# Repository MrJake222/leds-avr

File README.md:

# AVR part of the LEDs project

This is the main project repo. Subfolders contain diffrent parts(LED-RGB, stove, etc.) and (to-be-refactored) common **MODBUS** code in *libs* folder.
**Eagle** folder contains schematics and boards made with *Eagle*

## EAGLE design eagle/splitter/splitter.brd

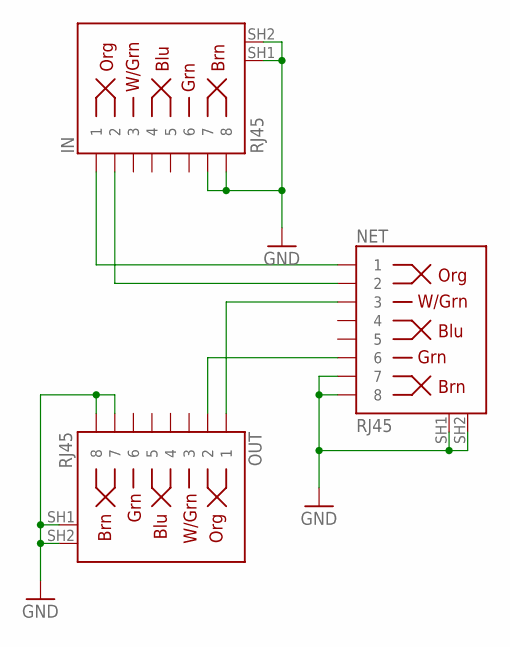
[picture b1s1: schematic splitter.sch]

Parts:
IN: RJ45; RJ45-8
NET: RJ45; RJ45-8
OUT: RJ45; RJ45-8

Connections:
GND: IN.7, IN.8, IN.SH1, IN.SH2, NET.7, NET.8, NET.SH1, NET.SH2, OUT.7, OUT.8, OUT.SH1, OUT.SH2
IN_A: IN.1, NET.1
IN_B: IN.2, NET.2
OUT_A: NET.3, OUT.1
OUT_B: NET.6, OUT.2

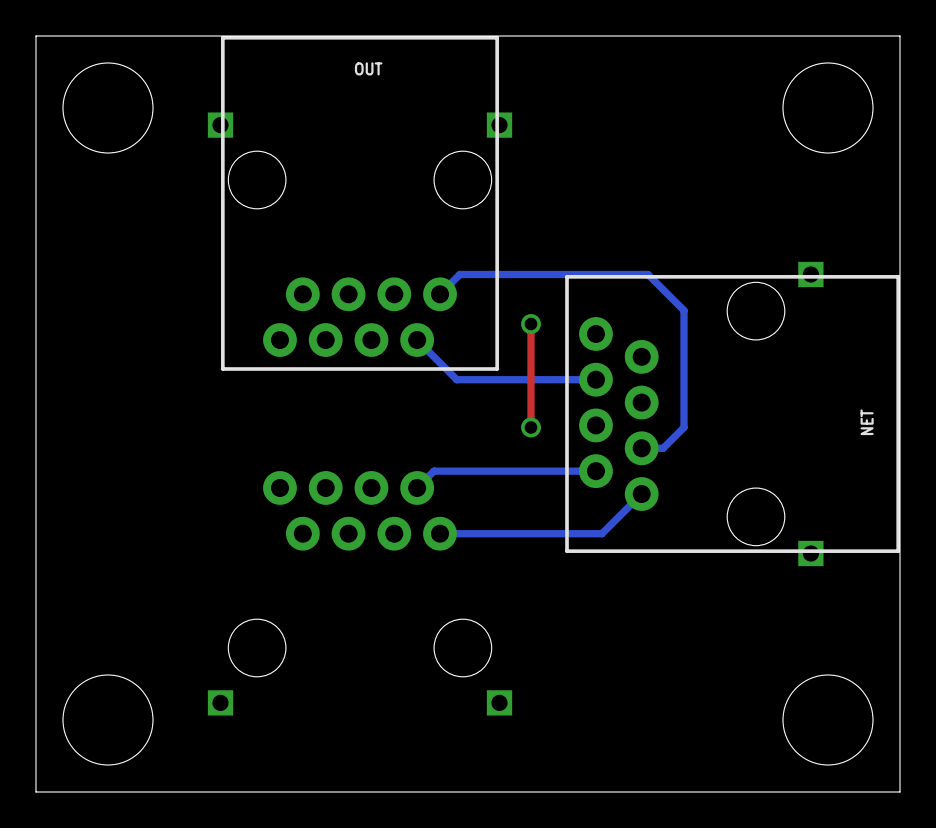
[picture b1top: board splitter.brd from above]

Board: 2 copper layers, 48.0 x 42.0 mm, 3 parts (1 on the bottom side), 5 nets.

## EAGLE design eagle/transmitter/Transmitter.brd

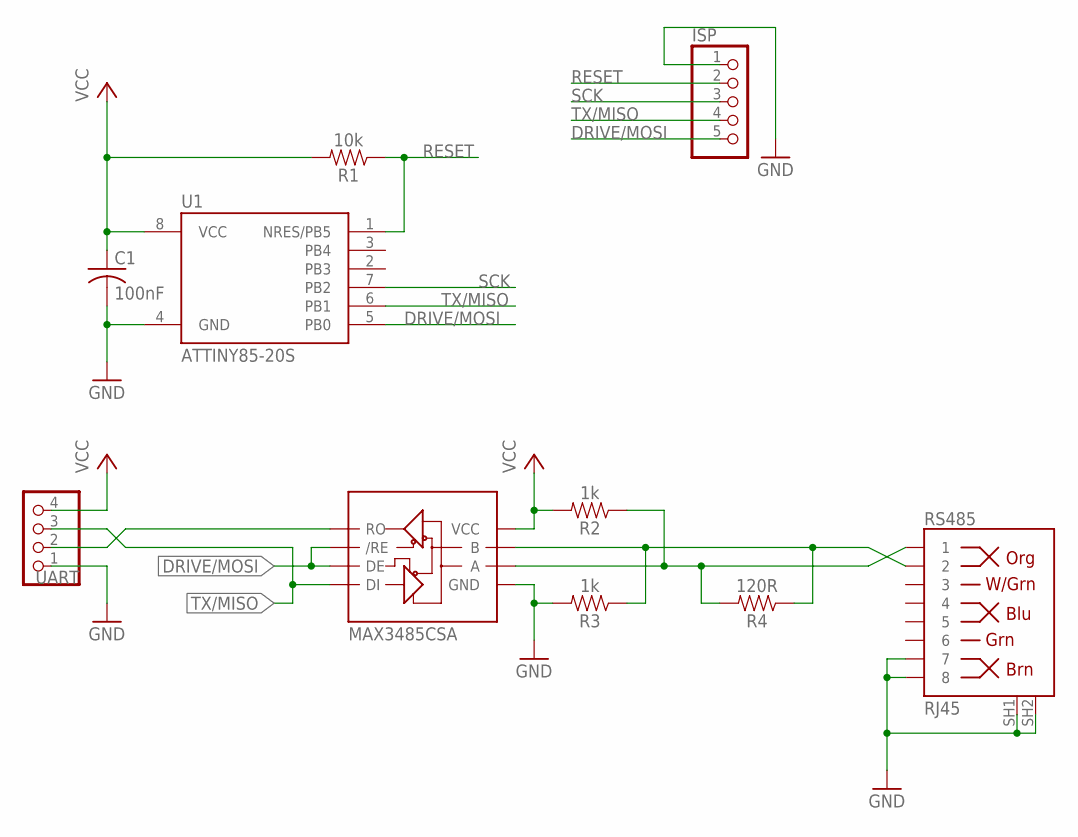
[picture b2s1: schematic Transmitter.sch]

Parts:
C1: 100nF; C0603; MPN CC0201KRX5R5BB104
ISP: PINHD-1X5; 1X05
R1: 10k; 0603
R2, R3: 1k; 0603
R4: 120R; 0805
RS485: RJ45; RJ45-8
U1: ATTINY85-20S; SOIC8_EIAJ_208MIL
U2: MAX3485CSA; SO08
UART: PINHD-1X4; 1X04

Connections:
A: R2.1, R4.2, RS485.1, U2.6 (A)
B: R3.1, R4.1, RS485.2, U2.7 (B)
DRIVE/MOSI: ISP.5, U1.5 (PB0), U2.2 (/RE), U2.3 (DE)
GND: C1.2, ISP.1, R3.2, RS485.7, RS485.8, RS485.SH1, RS485.SH2, U1.4 (GND), U2.5 (GND), UART.1
RESET: ISP.2, R1.1, U1.1 (NRES/PB5)
RX: U2.1 (RO), UART.2
SCK: ISP.3, U1.7 (PB2)
TX/MISO: ISP.4, U1.6 (PB1), U2.4 (DI), UART.3
VCC: C1.1, R1.2, R2.2, U1.8 (VCC), U2.8 (VCC), UART.4

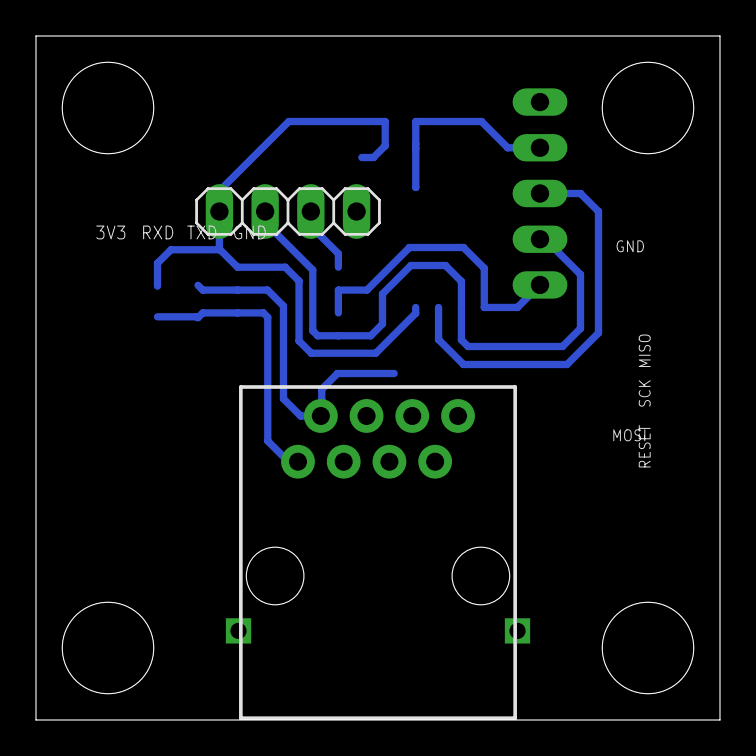
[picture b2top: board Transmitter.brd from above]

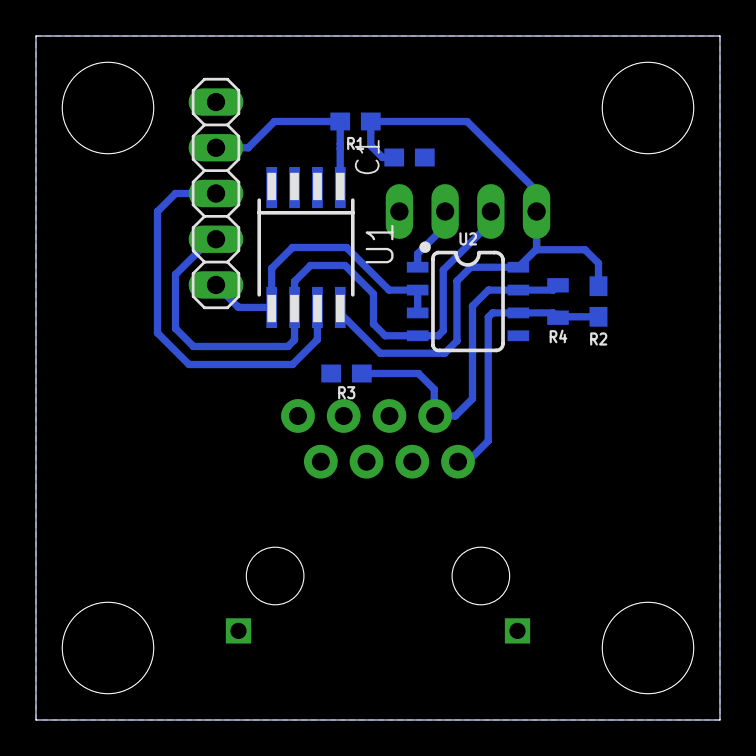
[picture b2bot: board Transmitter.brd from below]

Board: 2 copper layers, 38.0 x 38.0 mm, 10 parts (8 on the bottom side), 9 nets.

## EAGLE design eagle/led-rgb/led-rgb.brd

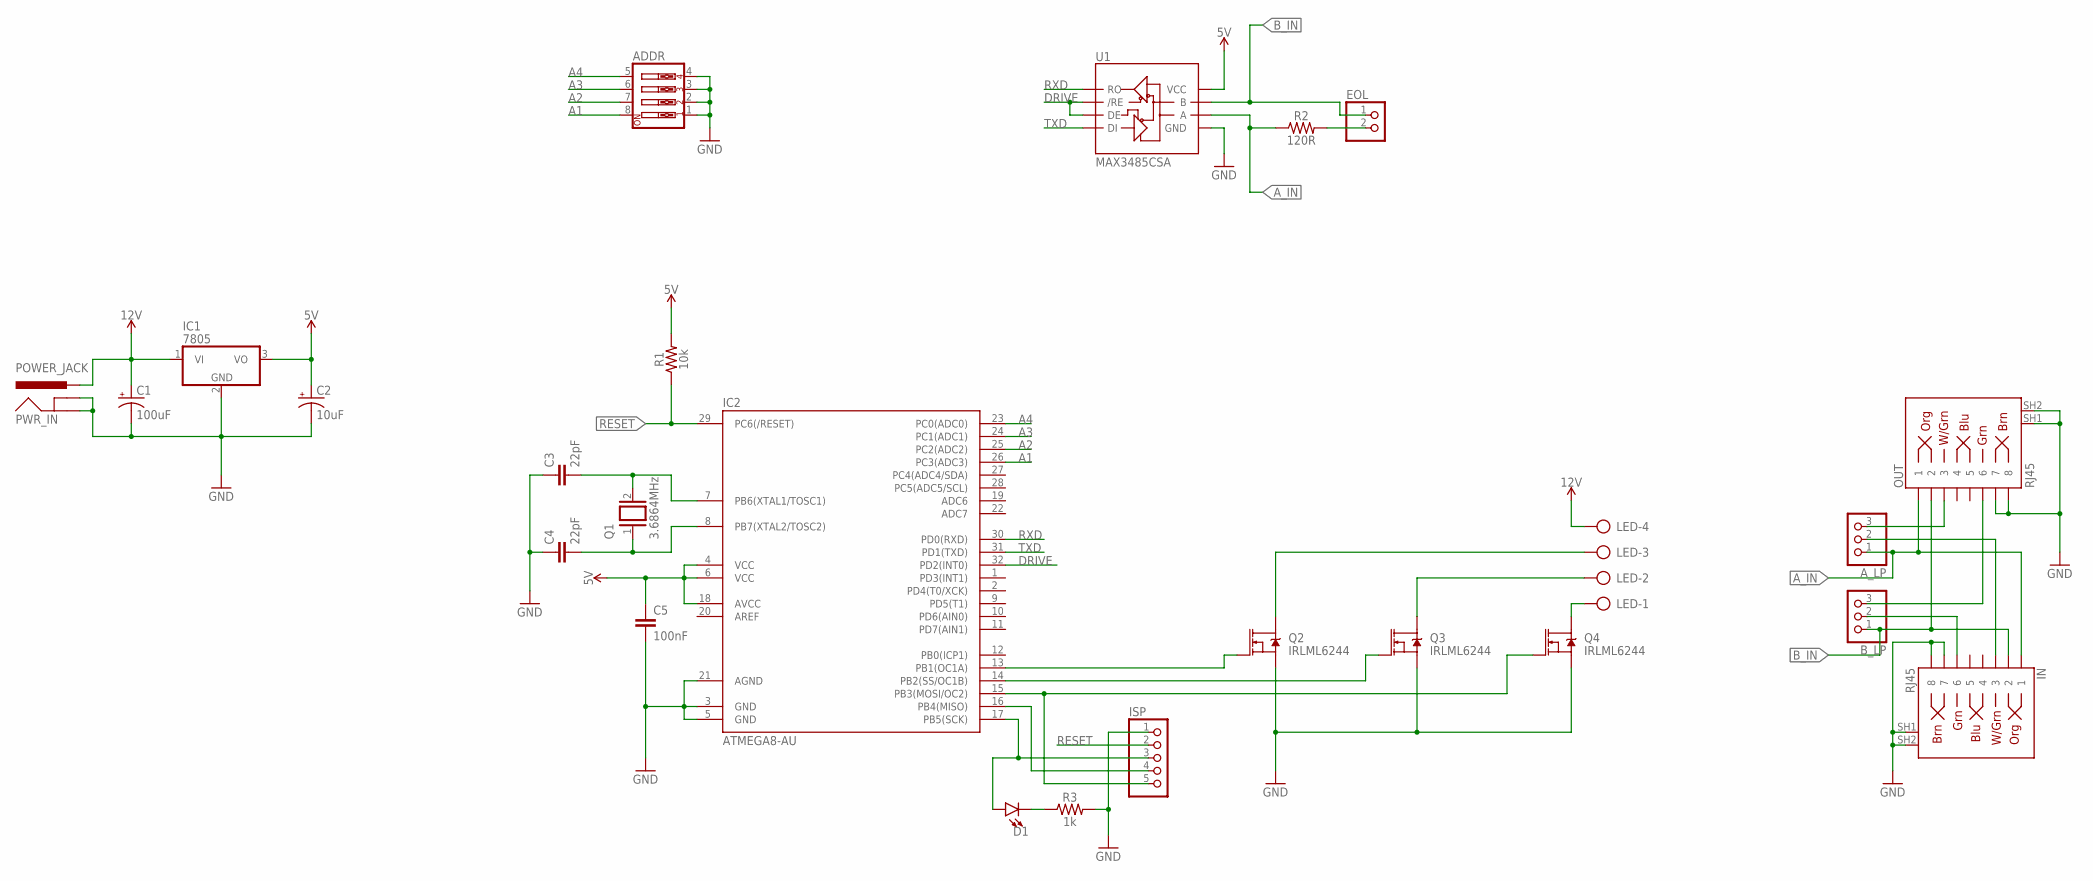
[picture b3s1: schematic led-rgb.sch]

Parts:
ADDR: SW_DIP-4; EDG-04
A_LP: PINHD-1X3; 1X03
B_LP: PINHD-1X3; 1X03
C1: 100uF; CPOL-RADIAL-2.5MM-6.5MM
C2: 10uF; CPOL-RADIAL-2.5MM-5MM
C3, C4: 22pF; C0805
C5: 100nF; C0603; MPN C0603X5R1C104K030BC
D1: LED3MM; LED_3MM
EOL: PINHD-1X2; 1X02; MPN V23026D1021B201 *X020
IC1: 7805; TO220V
IC2: ATMEGA8-AU; TQFP32-08
IN: RJ45; RJ45-8
ISP: PINHD-1X5; 1X05
LED: AK300/4
OUT: RJ45; RJ45-8
PWR_IN: POWER_JACK; POWER_JACK_PTH
Q1: 3.6864MHz; QS
Q2, Q3, Q4: IRLML6244; SOT23-3
R1: 10k; 0603
R2: 120R; 0805
R3: 1k; 0603
U1: MAX3485CSA; SO08

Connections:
5V: C2.1 (+), C5.1, IC1.3 (VO), IC2.4 (VCC), IC2.6 (VCC), IC2.18 (AVCC), R1.2, U1.8 (VCC)
12V: C1.1 (+), IC1.1 (VI), LED.4, PWR_IN.PWR
A1: ADDR.8, IC2.26 (PC3(ADC3))
A2: ADDR.7, IC2.25 (PC2(ADC2))
A3: ADDR.6, IC2.24 (PC1(ADC1))
A4: ADDR.5, IC2.23 (PC0(ADC0))
A-LOOP: A_LP.2, IN.3
A-LOOP-BACK: A_LP.3, OUT.3
A_IN: A_LP.1, IN.1, OUT.1, R2.1, U1.6 (A)
B-5V-MOSI: IC2.15 (PB3(MOSI/OC2)), ISP.5, Q4.1 (G)
B-12V: LED.1, Q4.3 (D)
B-LOOP: B_LP.2, IN.6
B-LOOP-BACK: B_LP.3, OUT.6
B_IN: B_LP.1, EOL.1, IN.2, OUT.2, U1.7 (B)
DRIVE: IC2.32 (PD2(INT0)), U1.2 (/RE), U1.3 (DE)
EOL1: EOL.2, R2.2
G-5V: IC2.13 (PB1(OC1A)), Q2.1 (G)
G-12V: LED.3, Q2.3 (D)
GND: ADDR.1, ADDR.2, ADDR.3, ADDR.4, C1.2 (-), C2.2 (-), C3.1, C4.1, C5.2, IC1.2 (GND), IC2.3 (GND), IC2.5 (GND), IC2.21 (AGND), IN.7, IN.8, IN.SH1, IN.SH2, ISP.1, OUT.7, OUT.8, OUT.SH1, OUT.SH2, PWR_IN.GND, PWR_IN.GNDBREAK, Q2.2 (S), Q3.2 (S), Q4.2 (S), R3.2, U1.5 (GND)
MISO: IC2.16 (PB4(MISO)), ISP.4
unnamed: D1.K (C), R3.1
R-5V: IC2.14 (PB2(SS/OC1B)), Q3.1 (G)
R-12V: LED.2, Q3.3 (D)
RESET: IC2.29 (PC6(/RESET)), ISP.2, R1.1
RXD: IC2.30 (PD0(RXD)), U1.1 (RO)
SCK: D1.A, IC2.17 (PB5(SCK)), ISP.3
TXD: IC2.31 (PD1(TXD)), U1.4 (DI)
XTAL1: C3.2, IC2.7 (PB6(XTAL1/TOSC1)), Q1.2
XTAL2: C4.2, IC2.8 (PB7(XTAL2/TOSC2)), Q1.1

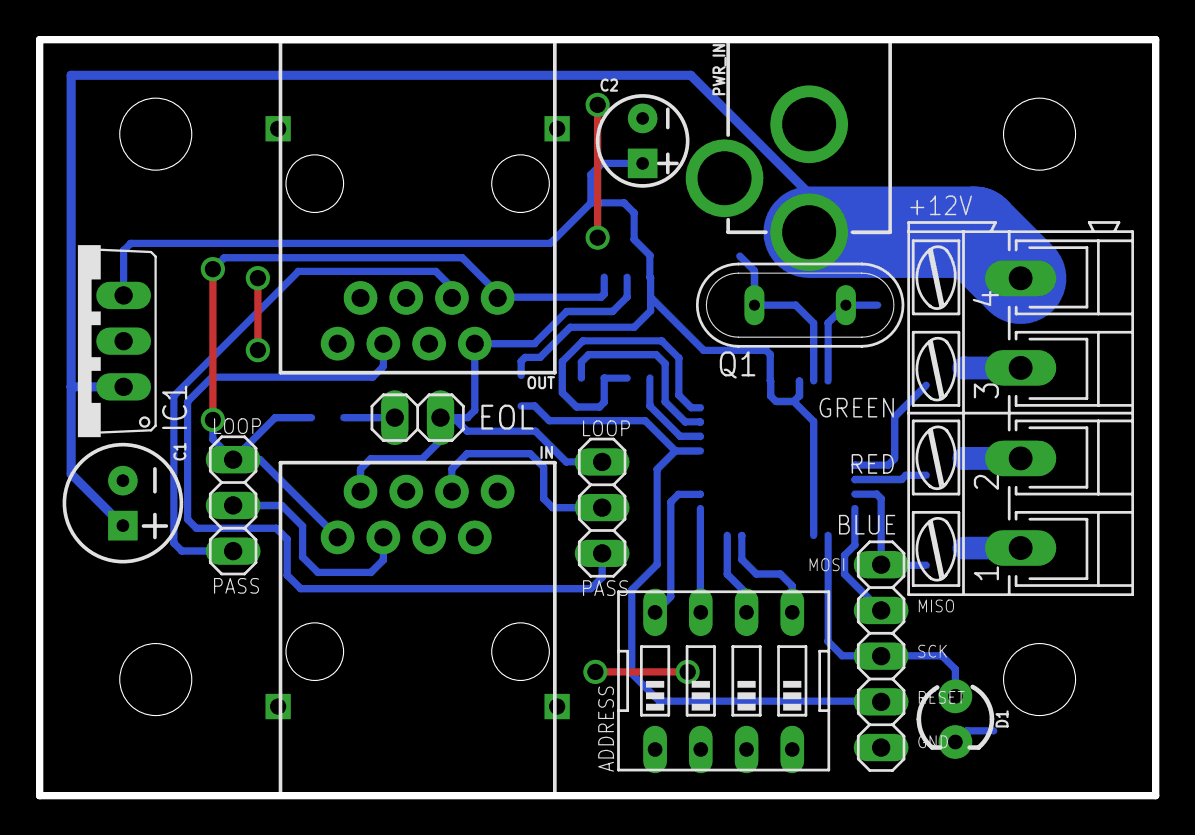
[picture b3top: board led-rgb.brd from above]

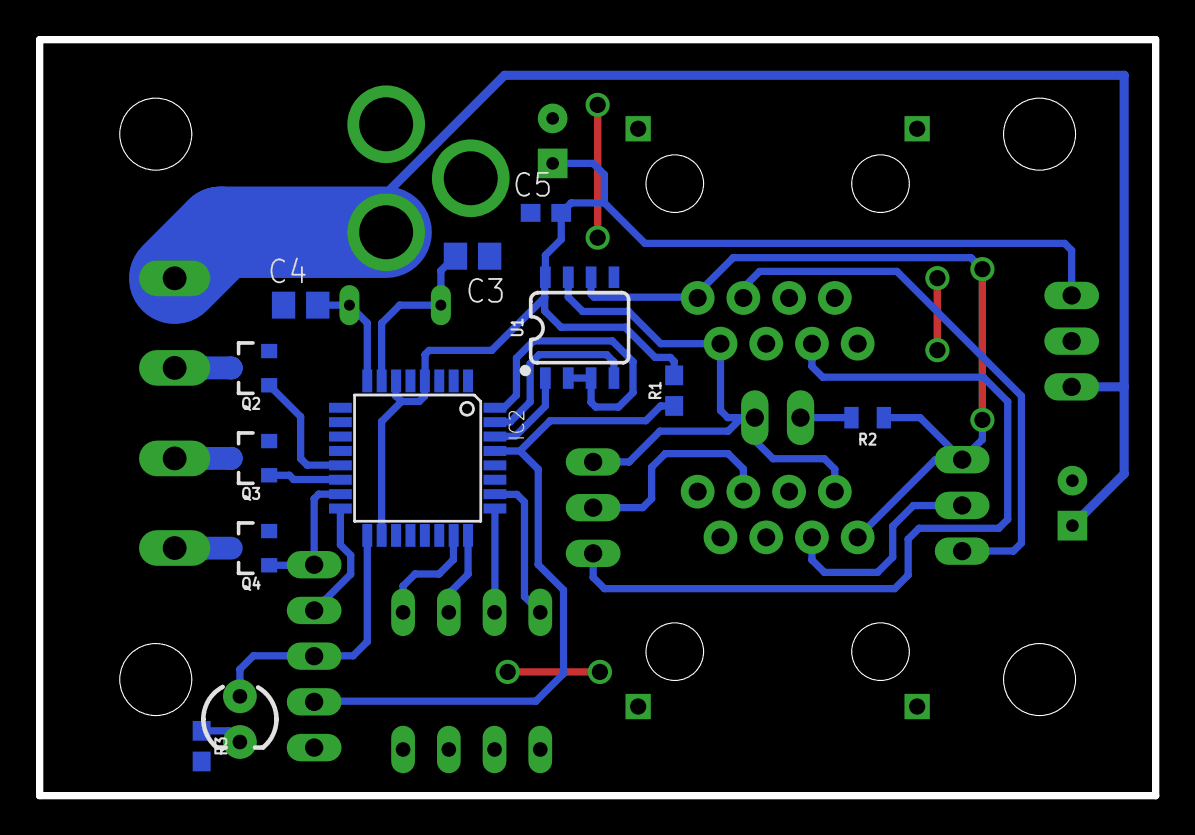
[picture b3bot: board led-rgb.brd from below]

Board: 2 copper layers, 62.0 x 42.0 mm, 25 parts (11 on the bottom side), 29 nets.

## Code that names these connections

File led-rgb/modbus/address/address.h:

#include <avr/io.h>
#include <util/delay.h>

#include <stdint.h>

// ------------------------------------------------------------ //

//#define PROTOTYPE

#ifndef PROTOTYPE
	#define A1_DIR		DDRC
	#define A1_PORT		PORTC
	#define A1_PIN		PINC
	#define A1_NUM		PC3

	#define A2_DIR		DDRC
	#define A2_PORT		PORTC
	#define A2_PIN		PINC
	#define A2_NUM		PC2

	#define A3_DIR		DDRC
	#define A3_PORT		PORTC
	#define A3_PIN		PINC
	#define A3_NUM		PC1

	#define A4_DIR		DDRC
	#define A4_PORT		PORTC
	#define A4_PIN		PINC
	#define A4_NUM		PC0

#else
	// Prototype 1

	#define A1_DIR		DDRC
	#define A1_PORT		PORTC
	#define A1_PIN		PINC
	#define A1_NUM		PC1

	#define A2_DIR		DDRC
	#define A2_PORT		PORTC
	#define A2_PIN		PINC
	#define A2_NUM		PC0

	#define A3_DIR		DDRB
	#define A3_PORT		PORTB
	#define A3_PIN		PINB
	#define A3_NUM		PB5

	#define A4_DIR		DDRB
	#define A4_PORT		PORTB
	#define A4_PIN		PINB
	#define A4_NUM		PB4
#endif

// ------------------------------------------------------------ //
uint8_t readModbusAddress();

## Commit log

2019-11-14 Leds first version from Feb 2019
    One module, code needs refactoring and commenting
2019-12-09 1st rework
2019-12-23 Added read holding registers command
2020-01-05 Added address reset functionality
2020-01-05 Added Eagle files

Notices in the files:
parts and their libraries:
SparkFun-Capacitors: Licensing: Creative Commons ShareAlike 4.0 International - https://creativecommons.org/licenses/by-sa/4.0
